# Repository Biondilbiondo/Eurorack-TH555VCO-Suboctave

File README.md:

# TH555 SUB VCO

This is a remake of eurorack module for the excellent and fully-analog Thomas Henry 555 VCO [[1](https://electro-music.com/forum/topic-54623.html)] [[2](https://github.com/gerb-ster/TH-555-VCO)] [[3](https://www.eddybergman.com/2020/12/synthesizer-build-part-37-thomas-henry.html)].
I added some features and tweaks to the module (inventing very little...) to make it more appealing to be built in 2025.

1. Added a sub-octave stage chained with the module to generate a square, sawtooth and triangle waves 1 octave below, and a square wave 2 octaves below; this is basically taken from [[4](https://electro-music.com/wiki/pmwiki.php?n=Schematics.WaveThingMultiply-DivideWaveShapingCircuit)] 
2. Added an octave switch using a rotatory switch widely available in the DIY eurorack stores (the same of MTM turing machine [[5](https://www.musicthing.co.uk/Turing-Machine/)]
3. Drastically reduced the range of coarse/fine knobs to be used in combination with the octave switch (COARSE = +/- 2 octaves; FINE = +/- 3 semitones)
4. Added a LFO function, with larger range for the COARSE/FINE knobs, and a configurable basic frequence.
5. Switched input/output to thonkiconn
6. Removed the manually matched pair of transistors in favor of the in-chip matched BCM857BS
7. All components are now SMT (easy hand soldered SOIC, 0603 passives)

## Versions
# 0.1
First take, this version had several errors, both schematic copying errors and in the sub-octabve section. This version was used to develop v 0.2 but sources are lost.

# 0.2
Almost completely working version. 

Improvements wrt vs 0.1
- ✅ The clock feed circuit for the sub-octave is completely redesigned
- ✅ Several minor copying errors have been corrected
- ✅ The panel for octave switch has been corrected
- ✅ Resistors for the octave switch are now marked in the correct order
- ✅ All the trimmer are now in the same format (3214X) + name added for each
Problems:
- ❌ Transistors footprint is incorrect (they shuld be mounted upside-down)
- ❌ The frontpanel interface is not optimal
- ❌ Octave switch is not properly tuned depending on the fluctuation of resistors
- ❌ Calibration is not easy

Also this version was lost.

# 0.3
This version is the current one, waiting to be built, it was designed starting from reverse-eng of v0.2 from production files. 

Improvements wrt vs 0.2
- ✅ Front panel redesign 
- ✅ Added leds to visualize the wave
- ✅ Corrected footprint of transistors
- ✅ Added a trimmer for octave-switch calibration

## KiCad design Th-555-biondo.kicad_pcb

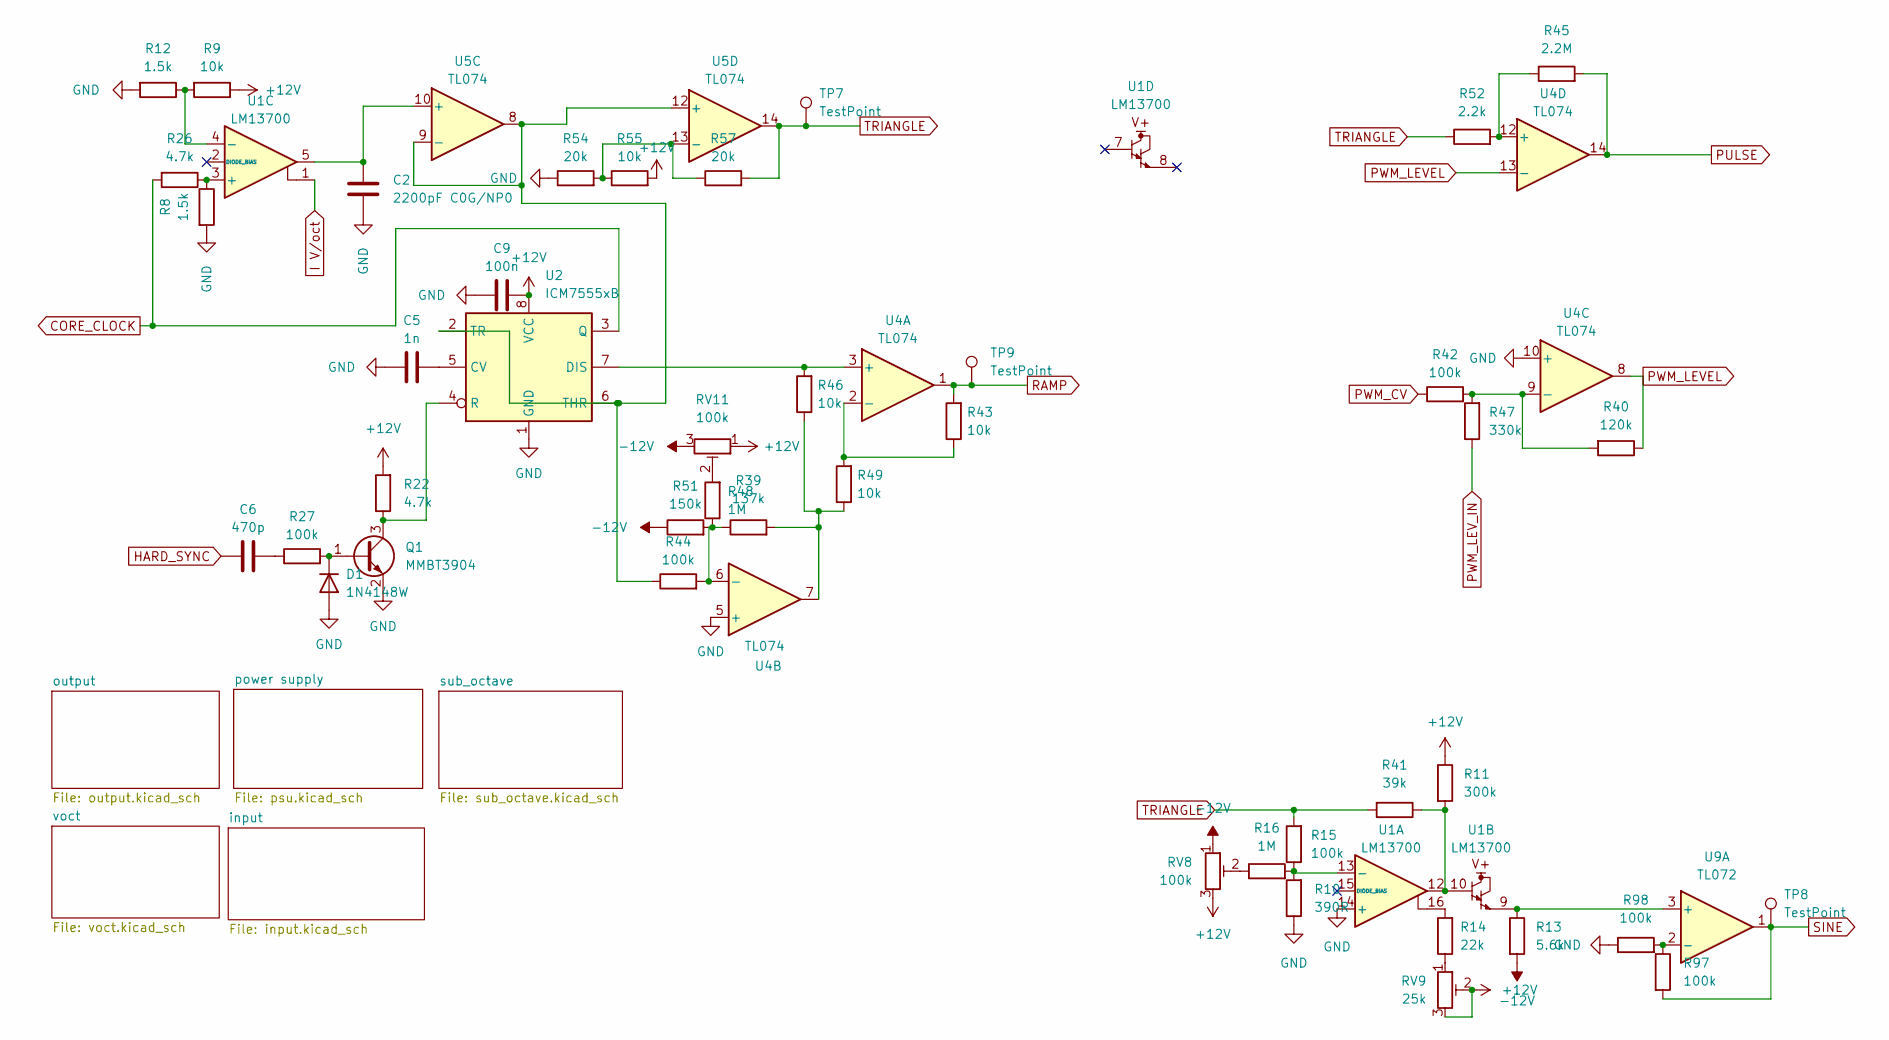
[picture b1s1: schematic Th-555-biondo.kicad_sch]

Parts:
C2: 2200pF C0G/NP0; C_0603_1608Metric_Pad1.08x0.95mm_HandSolder
C5: 1n; C_0603_1608Metric_Pad1.08x0.95mm_HandSolder
C6: 470p; C_0603_1608Metric_Pad1.08x0.95mm_HandSolder
C9: 100n; C_0603_1608Metric_Pad1.08x0.95mm_HandSolder
D1: 1N4148W; D_SOD-123
Q1: MMBT3904; SOT-23
R8, R12: 1.5k; R_0603_1608Metric_Pad0.98x0.95mm_HandSolder
R9, R43, R46, R49, R55: 10k; R_0603_1608Metric_Pad0.98x0.95mm_HandSolder
R10: 390R; R_0603_1608Metric_Pad0.98x0.95mm_HandSolder
R11: 300k; R_0603_1608Metric_Pad0.98x0.95mm_HandSolder
R13: 5.6k; R_0603_1608Metric_Pad0.98x0.95mm_HandSolder
R14: 22k; R_0603_1608Metric_Pad0.98x0.95mm_HandSolder
R15, R27, R42, R44, R97, R98: 100k; R_0603_1608Metric_Pad0.98x0.95mm_HandSolder
R16, R48: 1M; R_0603_1608Metric_Pad0.98x0.95mm_HandSolder
R22, R26: 4.7k; R_0603_1608Metric_Pad0.98x0.95mm_HandSolder
R39: 137k; R_0603_1608Metric_Pad0.98x0.95mm_HandSolder
R40: 120k; R_0603_1608Metric_Pad0.98x0.95mm_HandSolder
R41: 39k; R_0603_1608Metric_Pad0.98x0.95mm_HandSolder
R45: 2.2M; R_0603_1608Metric_Pad0.98x0.95mm_HandSolder
R47: 330k; R_0603_1608Metric_Pad0.98x0.95mm_HandSolder
R51: 150k; R_0603_1608Metric_Pad0.98x0.95mm_HandSolder
R52: 2.2k; R_0603_1608Metric_Pad0.98x0.95mm_HandSolder
R54, R57: 20k; R_0603_1608Metric_Pad0.98x0.95mm_HandSolder
RV8, RV11: 100k; Potentiometer_Bourns_3214X_Vertical
RV9: 25k; Potentiometer_Bourns_3214X_Vertical
TP7, TP8, TP9: TestPoint; TestPoint_Pad_D1.0mm
U1: LM13700; SOIC-16_3.9x9.9mm_P1.27mm
U2: ICM7555xB; SOIC-8_3.9x4.9mm_P1.27mm
U4, U5: TL074; SOIC-14_3.9x8.7mm_P1.27mm
U9: TL072; SOIC-8_3.9x4.9mm_P1.27mm

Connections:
+12V: C9.2, R9.1, R11.1, R22.2, R55.2, RV8.3, RV9.2, RV9.3, RV11.1, U2.8 (VCC); also elsewhere on the board
-12V: R13.2, R51.1, RV8.1, RV11.3; also elsewhere on the board
CORE_CLOCK: R26.2, U2.3 (Q); also elsewhere on the board
HARD_SYNC: C6.1; also elsewhere on the board
I V/oct: U1.1; also elsewhere on the board
unnamed: C6.2, R27.1
unnamed: D1.1 (K), Q1.1 (B), R27.2
unnamed: Q1.3 (C), R22.1, U2.4 (R)
unnamed: R11.2, R41.1, U1.10, U1.12
unnamed: R14.1, RV9.1
unnamed: R14.2, U1.16
unnamed: R16.1, RV8.2
unnamed: R39.2, R46.1, R49.1, U4.7
unnamed: R48.2, RV11.2
unnamed: R10.2, R15.1, R16.2, U1.13 (-)
unnamed: R8.1, R26.1, U1.3 (+)
unnamed: R9.2, R12.1, U1.4 (-)
unnamed: C5.2, U2.5 (CV)
unnamed: R46.2, U2.7 (DIS), U4.3 (+)
unnamed: R44.1, U2.2 (TR), U2.6 (THR), U5.8, U5.9 (-), U5.12 (+)
unnamed: R43.1, R49.2, U4.2 (-)
unnamed: R39.1, R44.2, R48.1, R51.2, U4.6 (-)
unnamed: R40.2, R42.2, R47.2, U4.9 (-)
unnamed: R45.1, R52.2, U4.12 (+)
unnamed: C2.1, U1.5, U5.10 (+)
unnamed: R54.2, R55.1, R57.1, U5.13 (-)
unnamed: R13.1, U1.9, U9.3 (+)
unnamed: R97.1, R98.2, U9.2 (-)
PULSE: R45.2, U4.14; also elsewhere on the board
PWM_CV: R42.1; also elsewhere on the board
PWM_LEVEL: R40.1, U4.8, U4.13 (-); also elsewhere on the board
PWM_LEV_IN: R47.1; also elsewhere on the board
RAMP: R43.2, TP9.1, U4.1; also elsewhere on the board
SINE: R97.2, TP8.1, U9.1; also elsewhere on the board
TRIANGLE: R15.2, R41.2, R52.1, R57.2, TP7.1, U5.14; also elsewhere on the board

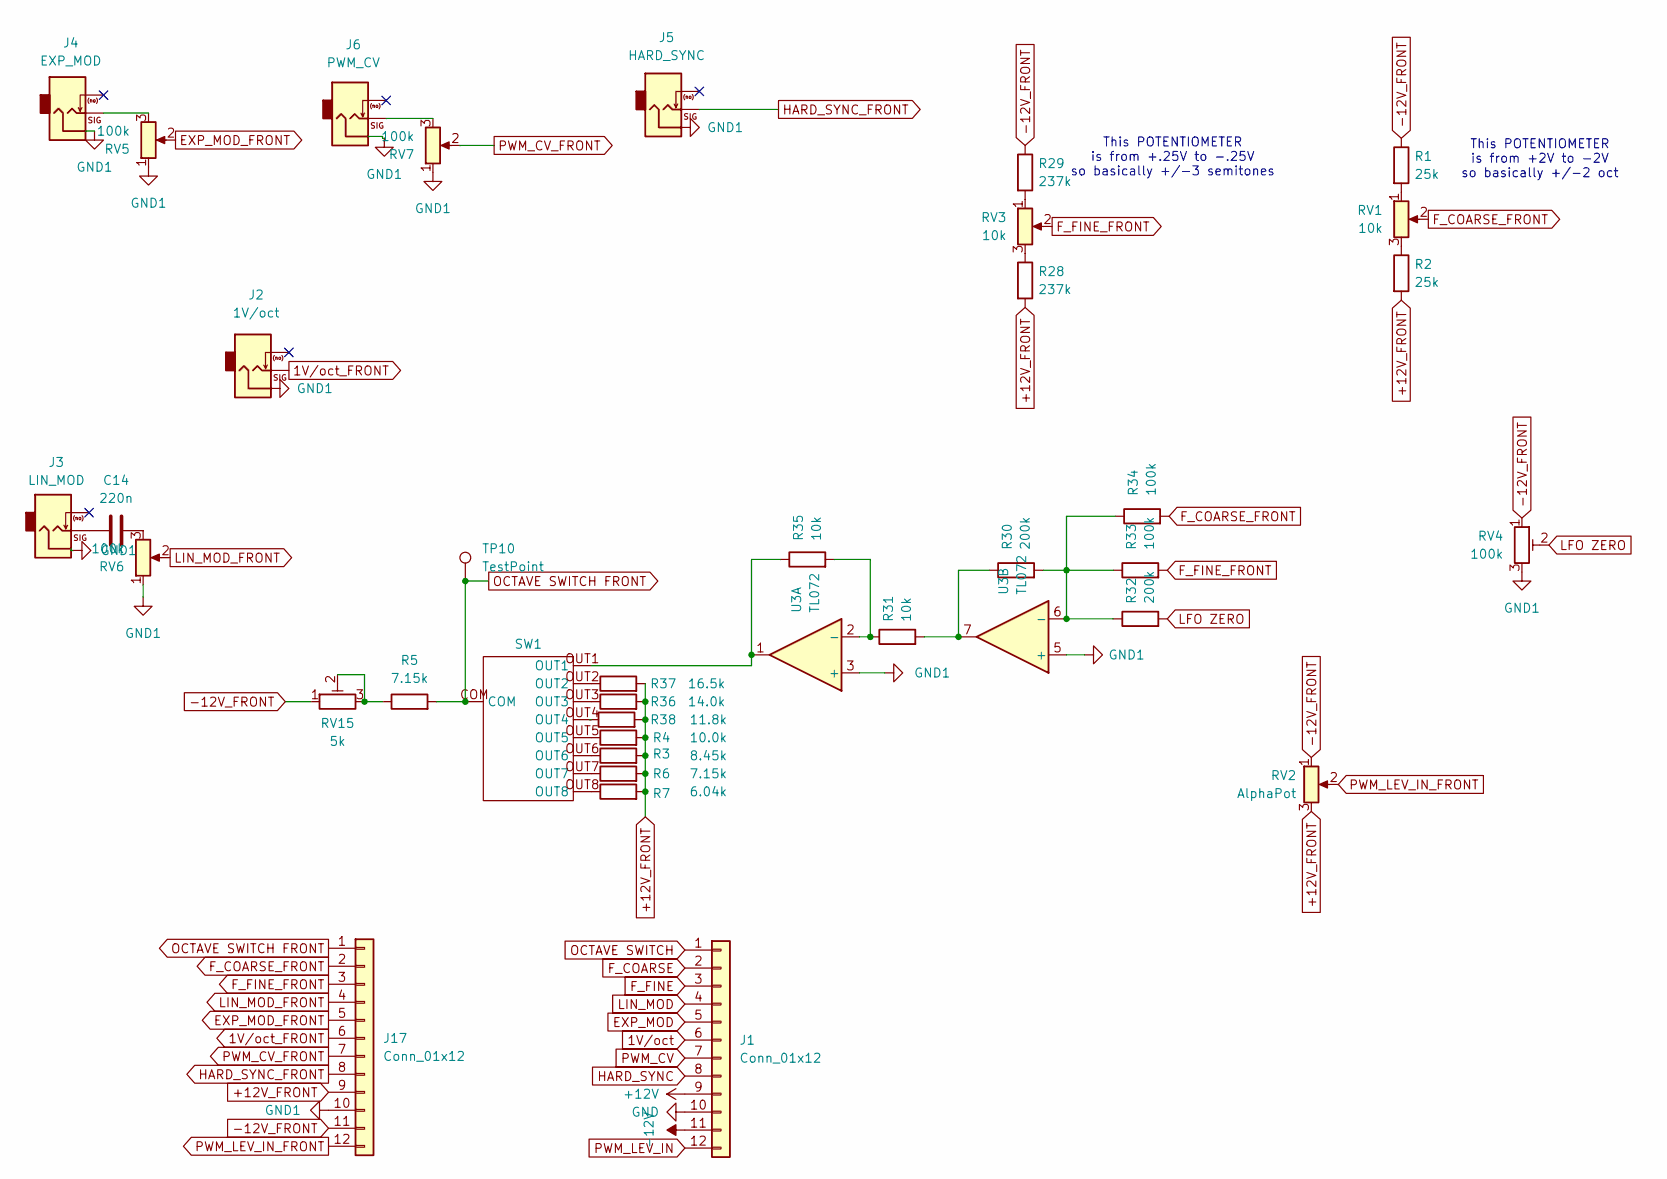
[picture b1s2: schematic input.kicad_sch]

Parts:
C14: 220n; C_0603_1608Metric_Pad1.08x0.95mm_HandSolder
J1: Conn_01x12; PinSocket_1x12_P2.54mm_Vertical
J2: 1V/oct; Jack_3.5mm_QingPu_WQP-PJ398SM_Vertical_CircularHoles
J3: LIN_MOD; Jack_3.5mm_QingPu_WQP-PJ398SM_Vertical_CircularHoles
J4: EXP_MOD; Jack_3.5mm_QingPu_WQP-PJ398SM_Vertical_CircularHoles
J5: HARD_SYNC; Jack_3.5mm_QingPu_WQP-PJ398SM_Vertical_CircularHoles
J6: PWM_CV; Jack_3.5mm_QingPu_WQP-PJ398SM_Vertical_CircularHoles
J17: Conn_01x12; PinHeader_1x12_P2.54mm_Vertical
R1, R2: 25k; R_0603_1608Metric_Pad0.98x0.95mm_HandSolder
R3: 8.45k; R_0603_1608Metric_Pad0.98x0.95mm_HandSolder
R4: 10.0k; R_0603_1608Metric_Pad0.98x0.95mm_HandSolder
R5, R6: 7.15k; R_0603_1608Metric_Pad0.98x0.95mm_HandSolder
R7: 6.04k; R_0603_1608Metric_Pad0.98x0.95mm_HandSolder
R28, R29: 237k; R_0603_1608Metric_Pad0.98x0.95mm_HandSolder
R30, R32: 200k; R_0603_1608Metric_Pad0.98x0.95mm_HandSolder
R31, R35: 10k; R_0603_1608Metric_Pad0.98x0.95mm_HandSolder
R33, R34: 100k; R_0603_1608Metric_Pad0.98x0.95mm_HandSolder
R36: 14.0k; R_0603_1608Metric_Pad0.98x0.95mm_HandSolder
R37: 16.5k; R_0603_1608Metric_Pad0.98x0.95mm_HandSolder
R38: 11.8k; R_0603_1608Metric_Pad0.98x0.95mm_HandSolder
RV1, RV3: 10k; Potentiometer_Alpha_RD901F-40-00D_Single_Vertical
RV2: AlphaPot; Potentiometer_Alpha_RD901F-40-00D_Single_Vertical
RV4: 100k; Potentiometer_Bourns_3214X_Vertical
RV5, RV6, RV7: 100k; Potentiometer_Alpha_RD901F-40-00D_Single_Vertical
RV15: 5k; Potentiometer_Bourns_3214X_Vertical
SW1: TH_rot_switch
TP10: TestPoint; TestPoint_Pad_D1.0mm
U3: TL072; SOIC-8_3.9x4.9mm_P1.27mm

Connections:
1V/oct: J1.6; also elsewhere on the board
1V/oct_FRONT: J2.T, J17.6
+12V: J1.9; also elsewhere on the board
+12V_FRONT: J17.9, R2.2, R3.2, R4.2, R6.2, R7.2, R28.2, R36.2, R37.2, R38.2, RV2.3; also elsewhere on the board
-12V: J1.11; also elsewhere on the board
-12V_FRONT: J17.11, R1.1, R29.1, RV2.1, RV4.1, RV15.1; also elsewhere on the board
EXP_MOD: J1.5; also elsewhere on the board
EXP_MOD_FRONT: J17.5, RV5.2
F_COARSE: J1.2; also elsewhere on the board
F_COARSE_FRONT: J17.2, R34.2, RV1.2
F_FINE: J1.3; also elsewhere on the board
F_FINE_FRONT: J17.3, R33.2, RV3.2
HARD_SYNC: J1.8; also elsewhere on the board
HARD_SYNC_FRONT: J5.T, J17.8
LFO ZERO: R32.2, RV4.2
LIN_MOD: J1.4; also elsewhere on the board
LIN_MOD_FRONT: J17.4, RV6.2
unnamed: C14.1, J3.T
unnamed: C14.2, RV6.3
unnamed: J4.T, RV5.3
unnamed: J6.T, RV7.3
unnamed: R1.2, RV1.1
unnamed: R2.1, RV1.3
unnamed: R3.1, SW1.OUT6
unnamed: R4.1, SW1.OUT5
unnamed: R5.1, RV15.2, RV15.3
unnamed: R6.1, SW1.OUT7
unnamed: R7.1, SW1.OUT8
unnamed: R28.1, RV3.3
unnamed: R29.2, RV3.1
unnamed: R30.1, R31.2, U3.7
unnamed: R35.1, SW1.OUT1, U3.1
unnamed: R36.1, SW1.OUT3
unnamed: R37.1, SW1.OUT2
unnamed: R38.1, SW1.OUT4
unnamed: R31.1, R35.2, U3.2 (-)
unnamed: R30.2, R32.1, R33.1, R34.1, U3.6 (-)
OCTAVE SWITCH: J1.1; also elsewhere on the board
OCTAVE SWITCH FRONT: J17.1, R5.2, SW1.COM, TP10.1
PWM_CV: J1.7; also elsewhere on the board
PWM_CV_FRONT: J17.7, RV7.2
PWM_LEV_IN: J1.12; also elsewhere on the board
PWM_LEV_IN_FRONT: J17.12, RV2.2

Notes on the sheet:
This POTENTIOMETER is from +.25V to -.25V so basically +/-3 semitones
This POTENTIOMETER is from +2V to -2V so basically +/-2 oct

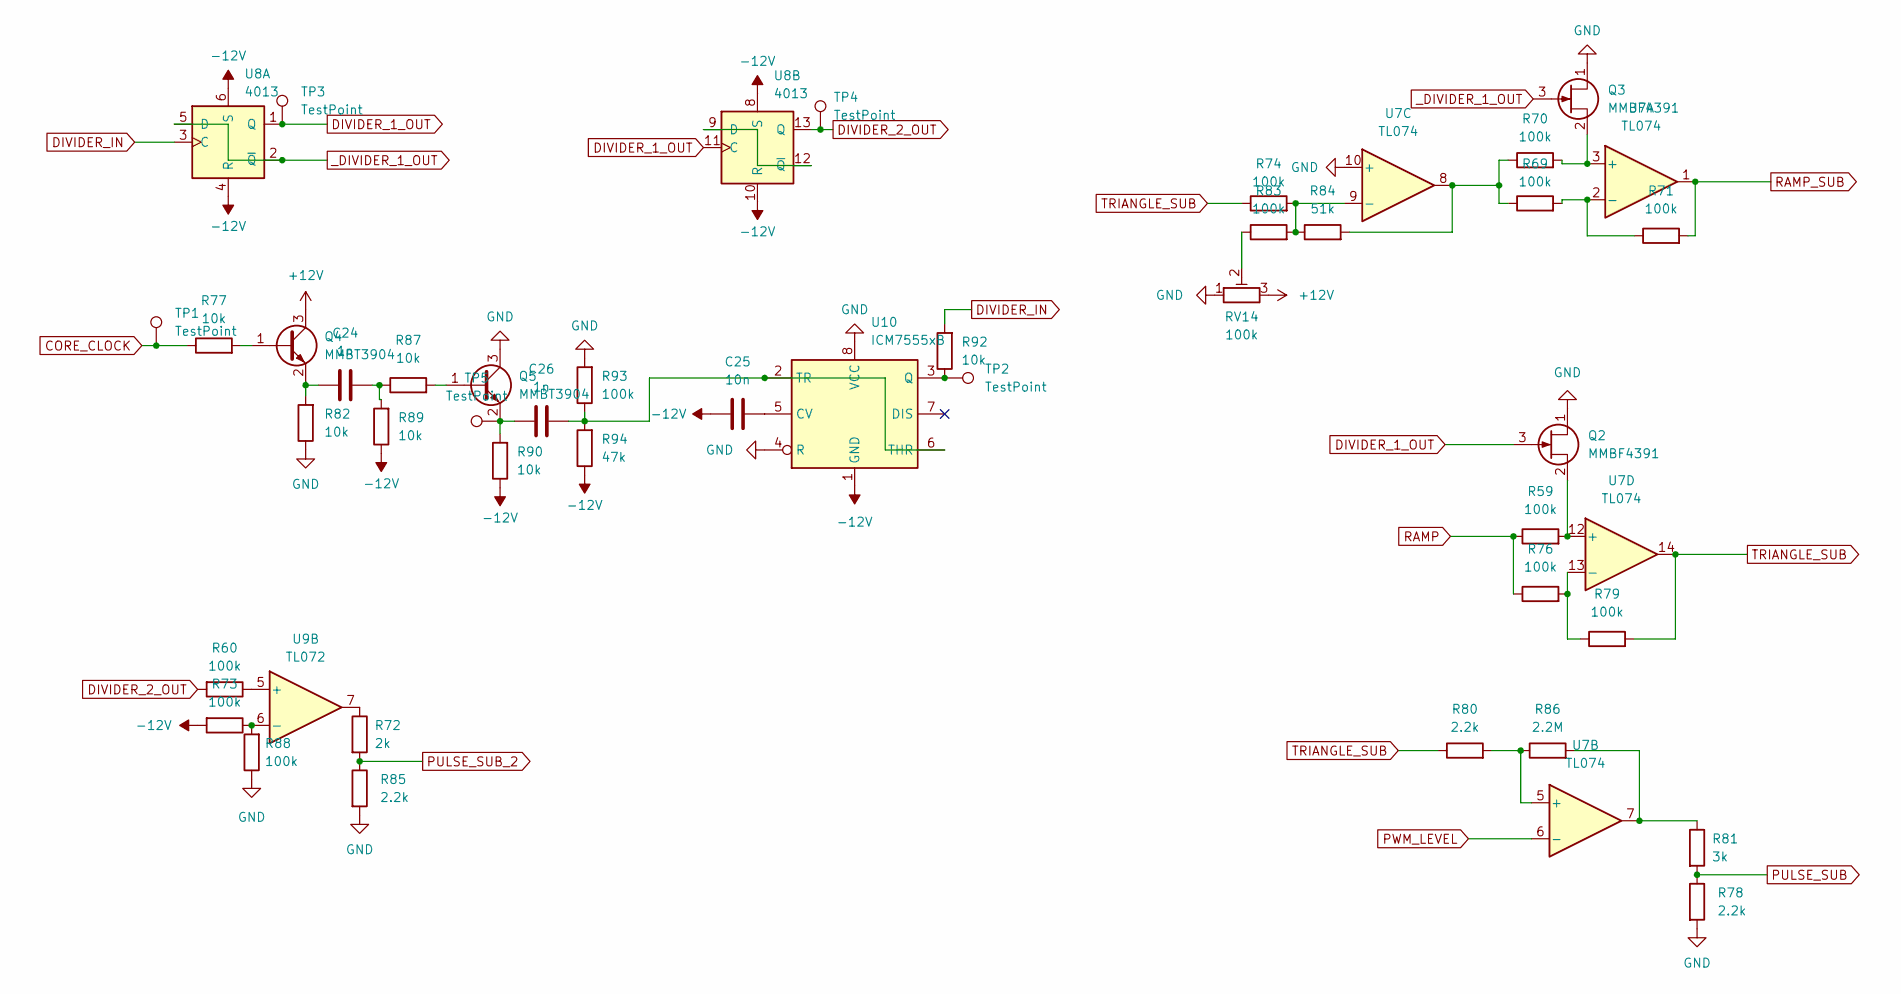
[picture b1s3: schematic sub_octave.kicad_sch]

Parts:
C24: 1n; C_0603_1608Metric
C25: 10n; C_0603_1608Metric
C26: 1n; C_0603_1608Metric_Pad1.08x0.95mm_HandSolder
Q2, Q3: MMBF4391; SOT-23
Q4, Q5: MMBT3904; SOT-23-3_npn
R59, R60, R69, R70, R71, R73, R74, R76, R79, R83, R88, R93: 100k; R_0603_1608Metric_Pad0.98x0.95mm_HandSolder
R72: 2k; R_0603_1608Metric_Pad0.98x0.95mm_HandSolder
R77, R82, R87, R89, R90, R92: 10k; R_0603_1608Metric_Pad0.98x0.95mm_HandSolder
R78, R80, R85: 2.2k; R_0603_1608Metric_Pad0.98x0.95mm_HandSolder
R81: 3k; R_0603_1608Metric_Pad0.98x0.95mm_HandSolder
R84: 51k; R_0603_1608Metric_Pad0.98x0.95mm_HandSolder
R86: 2.2M; R_0603_1608Metric_Pad0.98x0.95mm_HandSolder
R94: 47k; R_0603_1608Metric_Pad0.98x0.95mm_HandSolder
RV14: 100k; Potentiometer_Bourns_3214X_Vertical
TP1, TP2, TP3, TP4, TP5: TestPoint; TestPoint_Pad_D1.0mm
U7: TL074; SOIC-14_3.9x8.7mm_P1.27mm
U8: 4013; SOIC-14_3.9x8.7mm_P1.27mm
U9: TL072; SOIC-8_3.9x4.9mm_P1.27mm
U10: ICM7555xB; SOIC-8_3.9x4.9mm_P1.27mm

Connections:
+12V: Q4.3 (C), RV14.3; also elsewhere on the board
-12V: C25.1, R73.2, R89.1, R90.1, R94.1, U8.4 (R), U8.6 (S), U8.8 (S), U8.10 (R), U10.1 (GND); also elsewhere on the board
CORE_CLOCK: R77.1, TP1.1; also elsewhere on the board
DIVIDER_1_OUT: Q2.3 (G), TP3.1, U8.1 (Q), U8.11 (C)
DIVIDER_2_OUT: R60.2, TP4.1, U8.13 (Q)
DIVIDER_IN: R92.2, U8.3 (C)
unnamed: C24.2, R87.1, R89.2
unnamed: Q2.2 (S), R59.2, U7.12 (+)
unnamed: Q3.2 (S), R70.2, U7.3 (+)
unnamed: Q4.1 (B), R77.2
unnamed: C24.1, Q4.2 (E), R82.2
unnamed: Q5.1 (B), R87.2
unnamed: C26.1, Q5.2 (E), R90.2, TP5.1
unnamed: R69.1, R70.1, R84.2, U7.8
unnamed: R72.1, U9.7
unnamed: R81.1, R86.2, U7.7
unnamed: R83.1, RV14.2
unnamed: R69.2, R71.1, U7.2 (-)
unnamed: R80.2, R86.1, U7.5 (+)
unnamed: R74.2, R83.2, R84.1, U7.9 (-)
unnamed: R76.2, R79.1, U7.13 (-)
unnamed: U8.9 (D), U8.12 (~Q)
unnamed: R60.1, U9.5 (+)
unnamed: R73.1, R88.2, U9.6 (-)
unnamed: C25.2, U10.5 (CV)
unnamed: R92.1, TP2.1, U10.3 (Q)
unnamed: C26.2, R93.1, R94.2, U10.2 (TR), U10.6 (THR)
PULSE_SUB: R78.1, R81.2; also elsewhere on the board
PULSE_SUB_2: R72.2, R85.1; also elsewhere on the board
PWM_LEVEL: U7.6 (-); also elsewhere on the board
RAMP: R59.1, R76.1; also elsewhere on the board
RAMP_SUB: R71.2, U7.1
TRIANGLE_SUB: R74.1, R79.2, R80.1, U7.14; also elsewhere on the board
_DIVIDER_1_OUT: Q3.3 (G), U8.2 (~Q), U8.5 (D)

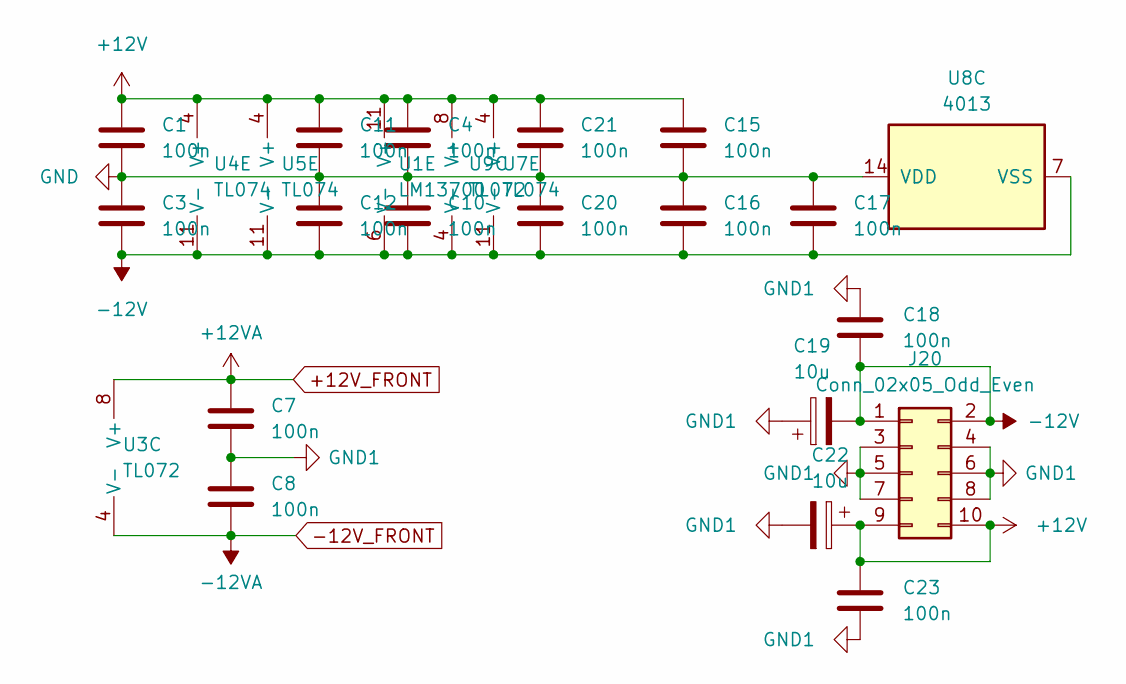
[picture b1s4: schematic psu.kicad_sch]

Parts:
C1, C3, C4, C7, C8, C10, C11, C12, C15, C16, C17, C18, C20, C21, C23: 100n; C_0603_1608Metric_Pad1.08x0.95mm_HandSolder
C19, C22: 10u; CP_Elec_4x5.8
J20: Conn_02x05_Odd_Even; IDC-Header_2x05_P2.54mm_Vertical
U1: LM13700; SOIC-16_3.9x9.9mm_P1.27mm
U3, U9: TL072; SOIC-8_3.9x4.9mm_P1.27mm
U4, U5, U7: TL074; SOIC-14_3.9x8.7mm_P1.27mm
U8: 4013; SOIC-14_3.9x8.7mm_P1.27mm

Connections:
+12V: C1.1, C4.1, C11.1, C15.1, C21.1, C22.1, C23.1, J20.9, J20.10, U1.11 (V+), U4.4 (V+), U5.4 (V+), U7.4 (V+), U9.8 (V+); also elsewhere on the board
+12V_FRONT: C7.1, U3.8 (V+); also elsewhere on the board
-12V: C3.2, C10.2, C12.2, C16.2, C17.2, C18.2, C19.2, C20.2, J20.1, J20.2, U1.6 (V-), U4.11 (V-), U5.11 (V-), U7.11 (V-), U8.7 (VSS), U9.4 (V-); also elsewhere on the board
-12V_FRONT: C8.2, U3.4 (V-); also elsewhere on the board

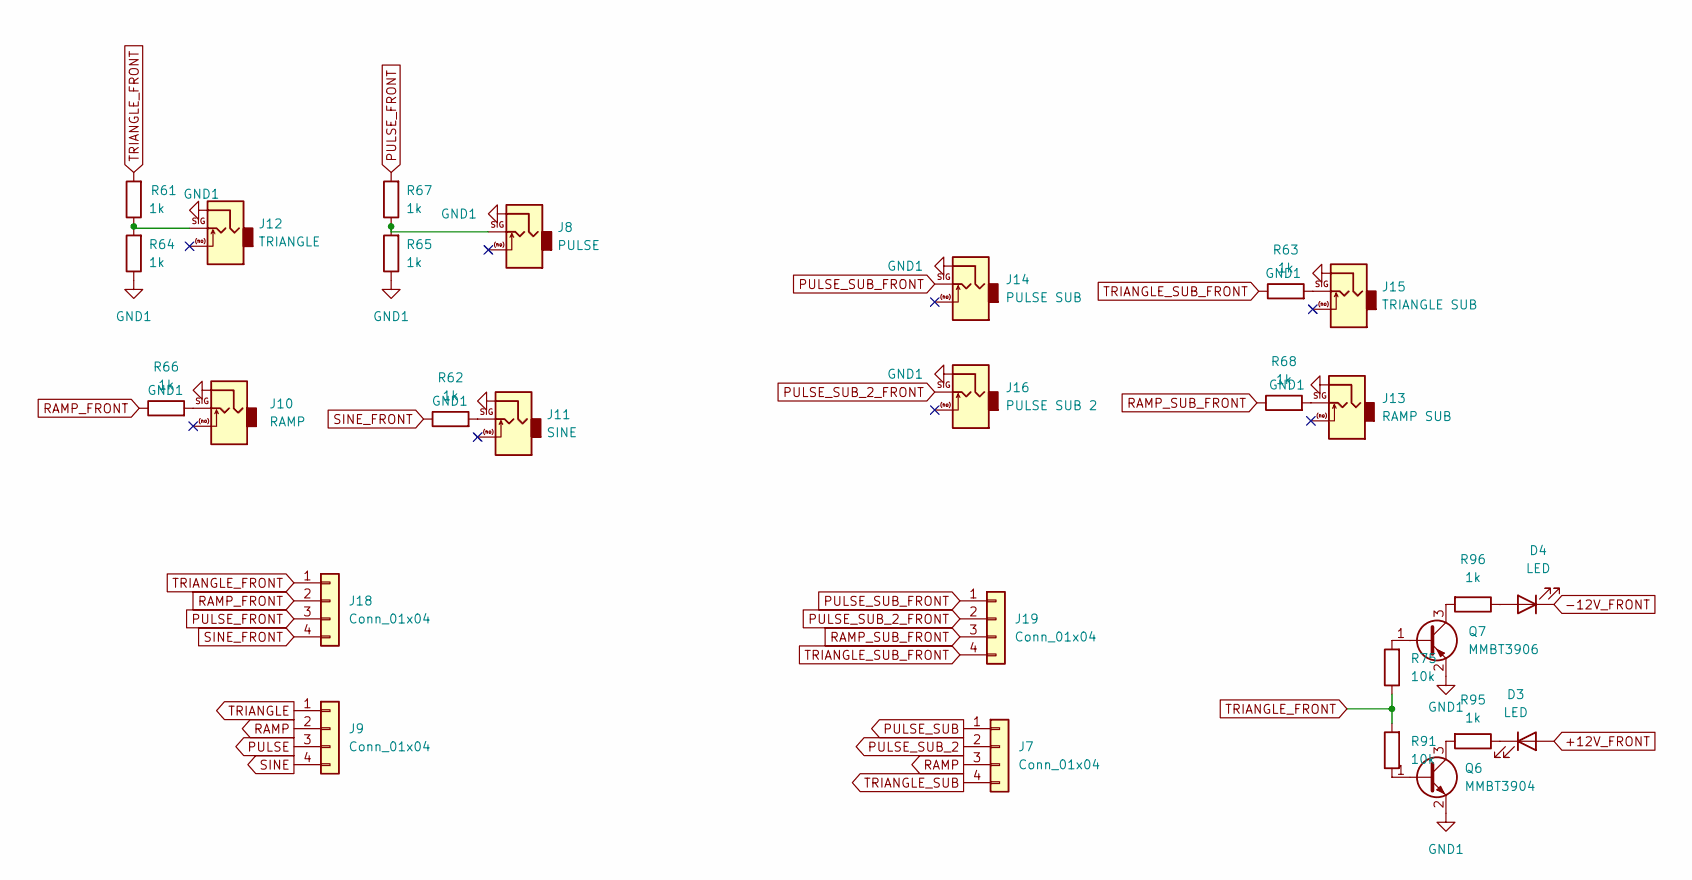
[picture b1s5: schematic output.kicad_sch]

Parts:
D3, D4: LED; LED_D3.0mm
J7, J9: Conn_01x04; PinSocket_1x04_P2.54mm_Vertical
J8: PULSE; Jack_3.5mm_QingPu_WQP-PJ398SM_Vertical_CircularHoles
J10: RAMP; Jack_3.5mm_QingPu_WQP-PJ398SM_Vertical_CircularHoles
J11: SINE; Jack_3.5mm_QingPu_WQP-PJ398SM_Vertical_CircularHoles
J12: TRIANGLE; Jack_3.5mm_QingPu_WQP-PJ398SM_Vertical_CircularHoles
J13: RAMP SUB; Jack_3.5mm_QingPu_WQP-PJ398SM_Vertical_CircularHoles
J14: PULSE SUB; Jack_3.5mm_QingPu_WQP-PJ398SM_Vertical_CircularHoles
J15: TRIANGLE SUB; Jack_3.5mm_QingPu_WQP-PJ398SM_Vertical_CircularHoles
J16: PULSE SUB 2; Jack_3.5mm_QingPu_WQP-PJ398SM_Vertical_CircularHoles
J18, J19: Conn_01x04; PinHeader_1x04_P2.54mm_Vertical
Q6: MMBT3904; SOT-23
Q7: MMBT3906; SOT-23
R61, R62, R63, R64, R65, R66, R67, R68, R95, R96: 1k; R_0603_1608Metric_Pad0.98x0.95mm_HandSolder
R75, R91: 10k; R_0603_1608Metric_Pad0.98x0.95mm_HandSolder

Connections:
+12V_FRONT: D3.2 (A); also elsewhere on the board
-12V_FRONT: D4.1 (K); also elsewhere on the board
unnamed: D3.1 (K), R95.1
unnamed: D4.2 (A), R96.1
unnamed: J8.T, R65.2, R67.1
unnamed: J10.T, R66.2
unnamed: J11.T, R62.2
unnamed: J12.T, R61.1, R64.2
unnamed: J13.T, R68.2
unnamed: J15.T, R63.2
unnamed: Q6.1 (B), R91.1
unnamed: Q6.3 (C), R95.2
unnamed: Q7.1 (B), R75.2
unnamed: Q7.3 (C), R96.2
PULSE: J9.3; also elsewhere on the board
PULSE_FRONT: J18.3, R67.2
PULSE_SUB: J7.1; also elsewhere on the board
PULSE_SUB_2: J7.2; also elsewhere on the board
PULSE_SUB_2_FRONT: J16.T, J19.2
PULSE_SUB_FRONT: J14.T, J19.1
RAMP: J7.3, J9.2; also elsewhere on the board
RAMP_FRONT: J18.2, R66.1
RAMP_SUB_FRONT: J19.3, R68.1
SINE: J9.4; also elsewhere on the board
SINE_FRONT: J18.4, R62.1
TRIANGLE: J9.1; also elsewhere on the board
TRIANGLE_FRONT: J18.1, R61.2, R75.1, R91.2
TRIANGLE_SUB: J7.4; also elsewhere on the board
TRIANGLE_SUB_FRONT: J19.4, R63.1

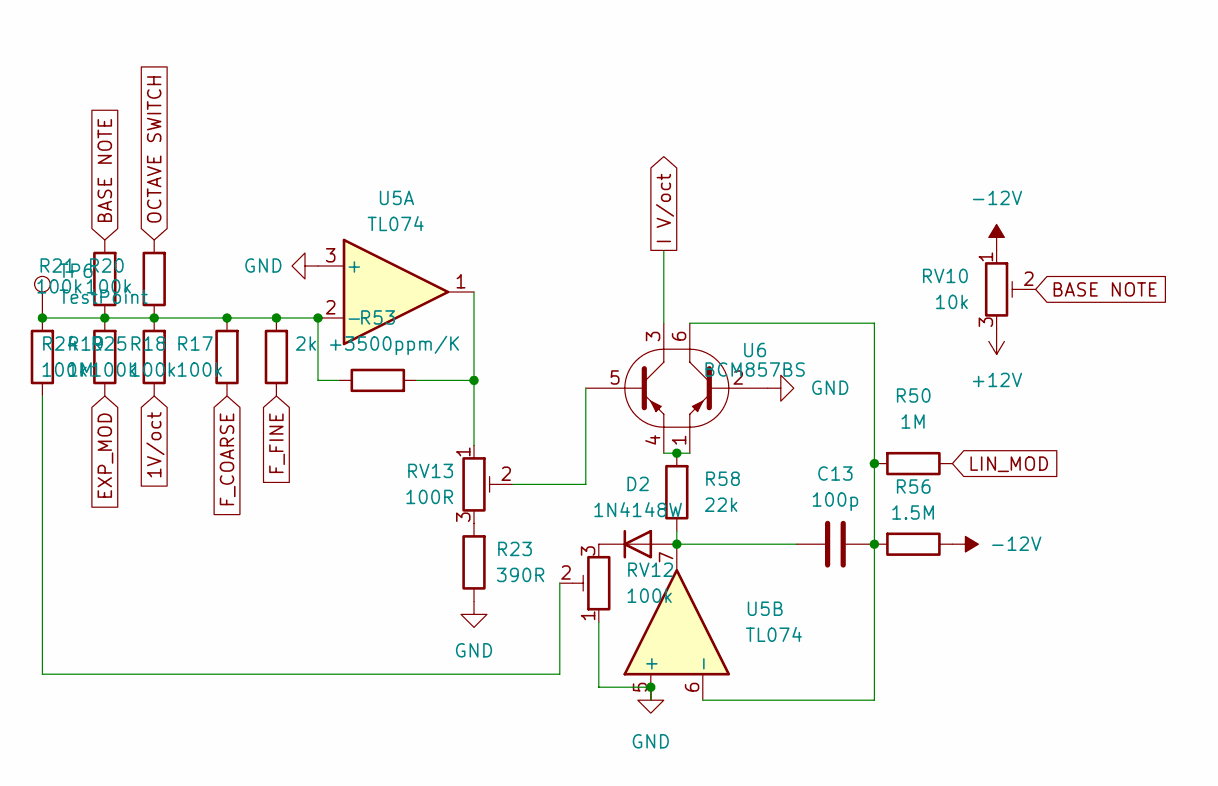
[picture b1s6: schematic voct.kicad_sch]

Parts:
C13: 100p; C_0603_1608Metric_Pad1.08x0.95mm_HandSolder
D2: 1N4148W; D_SOD-123
R17, R18, R20, R21, R24, R25: 100k; R_0603_1608Metric_Pad0.98x0.95mm_HandSolder
R19, R50: 1M; R_0603_1608Metric_Pad0.98x0.95mm_HandSolder
R23: 390R; R_0603_1608Metric_Pad0.98x0.95mm_HandSolder
R53: 2k +3500ppm/K; R_0603_1608Metric_Pad0.98x0.95mm_HandSolder
R56: 1.5M; R_0603_1608Metric_Pad0.98x0.95mm_HandSolder
R58: 22k; R_0603_1608Metric_Pad0.98x0.95mm_HandSolder
RV10: 10k; Potentiometer_Bourns_3214X_Vertical
RV12: 100k; Potentiometer_Bourns_3214X_Vertical
RV13: 100R; Potentiometer_Bourns_3214X_Vertical
TP6: TestPoint; TestPoint_Pad_D1.0mm
U5: TL074; SOIC-14_3.9x8.7mm_P1.27mm
U6: BCM857BS; SOT-363_SC-70-6

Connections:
1V/oct: R17.1; also elsewhere on the board
+12V: RV10.3; also elsewhere on the board
-12V: R56.1, RV10.1; also elsewhere on the board
BASE NOTE: R21.2, RV10.2
EXP_MOD: R18.1; also elsewhere on the board
F_COARSE: R24.1; also elsewhere on the board
F_FINE: R25.1; also elsewhere on the board
I V/oct: U6.3; also elsewhere on the board
LIN_MOD: R50.1; also elsewhere on the board
unnamed: C13.1, D2.2 (A), R58.1, U5.7
unnamed: D2.1 (K), RV12.3
unnamed: R19.1, RV12.2
unnamed: R23.2, RV13.3
unnamed: R53.2, RV13.1, U5.1
unnamed: R58.2, U6.1, U6.4
unnamed: RV13.2, U6.5
unnamed: R17.2, R18.2, R19.2, R20.1, R21.1, R24.2, R25.2, R53.1, TP6.1, U5.2 (-)
unnamed: C13.2, R50.2, R56.2, U5.6 (-), U6.6
OCTAVE SWITCH: R20.2; also elsewhere on the board

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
